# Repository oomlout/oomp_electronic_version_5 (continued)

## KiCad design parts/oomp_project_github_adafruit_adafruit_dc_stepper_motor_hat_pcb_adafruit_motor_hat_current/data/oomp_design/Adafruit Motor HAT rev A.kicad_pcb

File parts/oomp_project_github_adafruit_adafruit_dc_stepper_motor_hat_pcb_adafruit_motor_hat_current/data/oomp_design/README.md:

# OOMP KiCad design copy

Open `Adafruit Motor HAT rev A.kicad_pro` (or the `.kicad_pcb` / `.kicad_sch`) in KiCad. Local OOMP libraries are under `libraries/`. Original inputs are preserved in [../original/](../original/).

Only verified unchanged installed KiCad defaults were renamed. Modified, custom, unmatched and unavailable items remain unchanged. Soldering variants are never swapped during conversion. Existing pad coordinates, nets and UUIDs are preserved.

See [conversion_report.yaml](conversion_report.yaml) for every conversion and skip. Copy this directory before editing; regeneration refuses to overwrite edited design files.

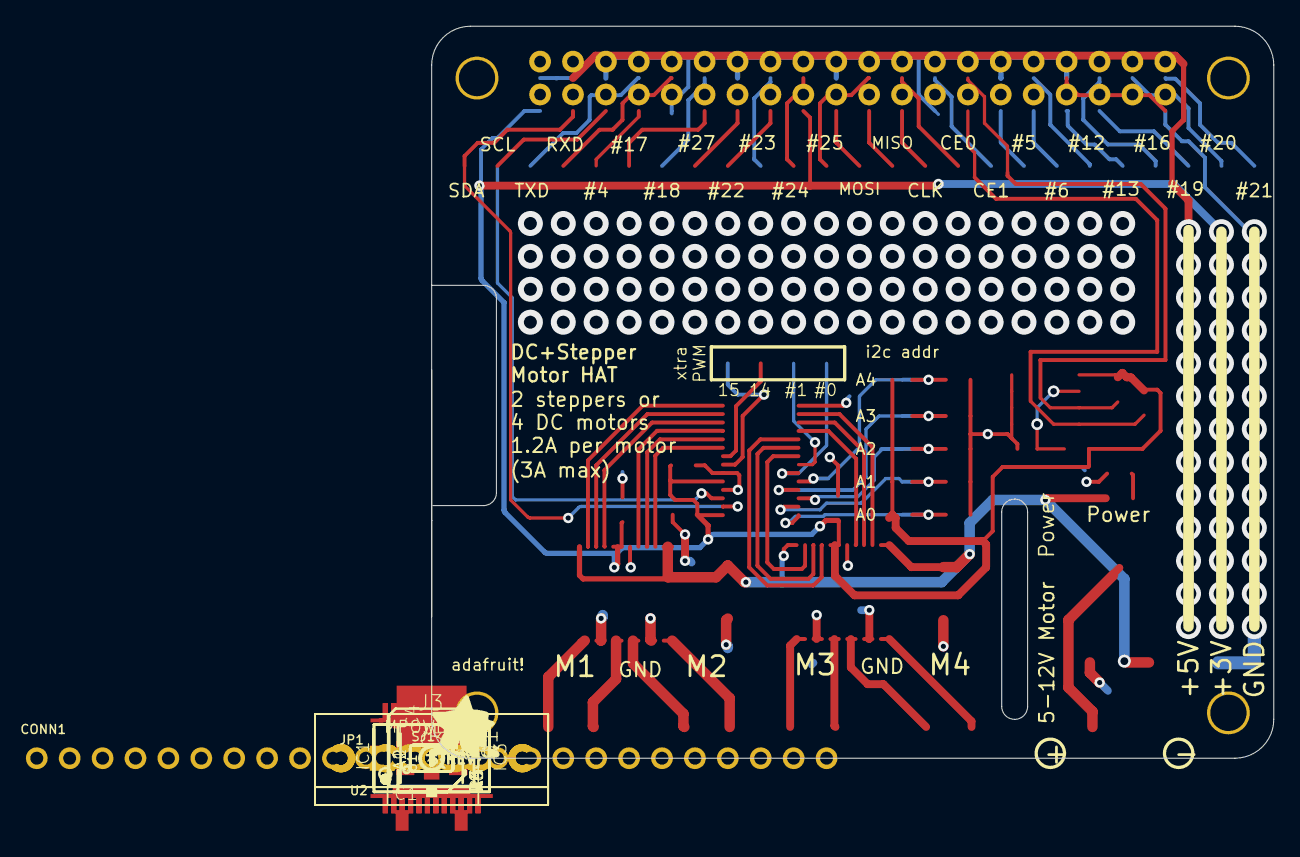
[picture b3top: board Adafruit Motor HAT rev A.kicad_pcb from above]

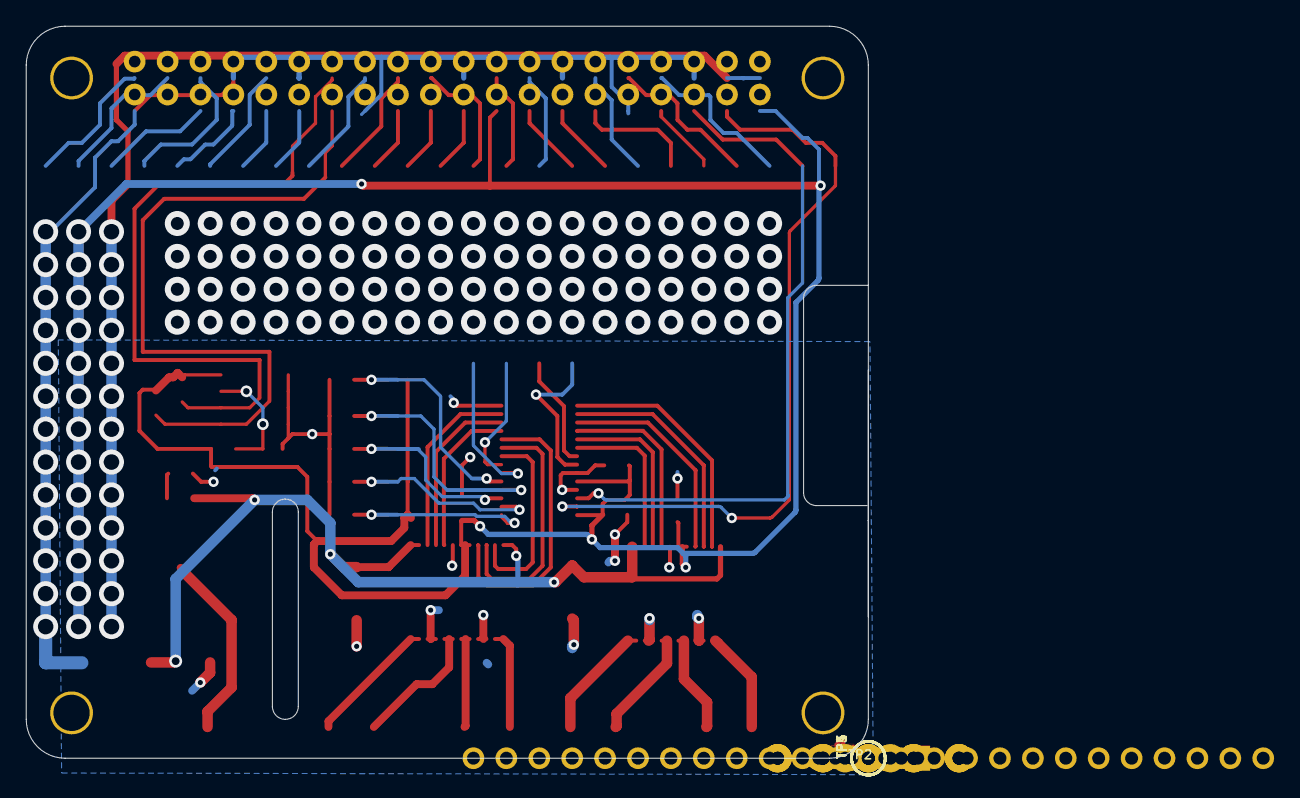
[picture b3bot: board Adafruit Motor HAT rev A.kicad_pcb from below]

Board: 2 copper layers, 65.0 x 56.5 mm, 44 parts (5 on the bottom side), 63 nets.

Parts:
A0, A1, A2, A3, A4: SOLDERJUMPER_REFLOW_NOPASTE
C1, C3: 0.1uF; 0805-NO
C4: 47uF/16v; PANASONIC_C
C5: 47uF+/16v; PANASONIC_C
C6, C10: 10uF; 0805-NO
CONN1: HEADER-1X25; 1X25_ROUND_70MIL
FID1, FID2, FID3: FIDUCIAL""; FIDUCIAL_1MM
IC1, IC3: TB6612FNG; SSOP24
J1, J3: 1X5; 1X05-3.5MM
JP1: 1X04_ROUND_76
LED1: Green; CHIPLED_0805_NOOUTLINE
MPOWER0: 1X2-3.5MM
Q1: AOD417; D-PAK_TO252AA
R1, R2, R3: 3.9K; 0805-NO
R4, R5, R6, R8, R9: 10k; 0805-NO
R7: 1K; 0805-NO
RPI1: RASPBERRYPI_BPLUS_HATSLOTS; PI_HAT_SLOTS
SJ1: WP; SOLDERJUMPER_CLOSEDWIRE
TP1, TP2, TP3, TP4, TP5: TESTPOINT_ROUND_2MM
U1: CAT24C32; SOIC8_150MIL
U2: PCA9685; TSSOP28
U$5: PIHATLOGO
U$6: PCBFEAT-REV-040
U$51: ADAFRUIT_5MM

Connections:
3.3V: A0.1, A1.1, A2.1, A3.2, A4.2, C1.1, C3.1, C6.1, C10.1, IC1.19, IC1.20, IC3.19, IC3.20, R1.2, R2.2, R3.2, RPI1.1, RPI1.17, U1.8, U2.24, U2.28
5.0V: RPI1.2, RPI1.4
+12V: C4.+, C5.+, IC1.13, IC1.14, IC1.24, IC3.13, IC3.14, IC3.24, LED1.A, Q1.3
A0: A0.2, R4.2, TP5.P$1, U2.1
A1: A1.2, R5.2, TP4.P$1, U2.2
A2: A2.2, R6.2, TP3.P$1, U2.3
A3: A3.1, R8.2, TP2.P$1, U2.4
A4: A4.1, R9.2, TP1.P$1, U2.5
EECLK: R2.1, RPI1.28, U1.6
EEDATA: R1.1, RPI1.27, U1.5
GND: C1.2, C3.2, C4.-, C5.-, C6.2, C10.2, IC1.3, IC1.4, IC1.9, IC1.10, IC1.18, IC3.3, IC3.4, IC3.9, IC3.10, IC3.18, J1.3, J3.3, MPOWER0.1, Q1.1, R4.1, R5.1, R6.1, R7.1, R8.1, R9.1, RPI1.6, RPI1.9, RPI1.14, RPI1.20, RPI1.25, RPI1.30, RPI1.34, RPI1.39, SJ1.1, U1.1, U1.2, U1.3, U1.4, U2.14, U2.23, U2.25
GPIO4: CONN1.5, RPI1.7
GPIO5: CONN1.18, RPI1.29
GPIO6: CONN1.19, RPI1.31
GPIO12: CONN1.20, RPI1.32
GPIO13: CONN1.21, RPI1.33
GPIO16: CONN1.22, RPI1.36
GPIO17: CONN1.6, RPI1.11
GPIO18: CONN1.7, RPI1.12
GPIO19: CONN1.23, RPI1.35
GPIO20: CONN1.24, RPI1.38
GPIO21: CONN1.25, RPI1.40
GPIO22: CONN1.9, RPI1.15
GPIO23: CONN1.10, RPI1.16
GPIO24: CONN1.11, RPI1.18
GPIO25: CONN1.12, RPI1.22
GPIO27: CONN1.8, RPI1.13
unnamed: MPOWER0.2, Q1.4
unnamed: IC1.1, IC1.2, J1.5
unnamed: IC1.5, IC1.6, J1.4
unnamed: IC1.7, IC1.8, J1.2
unnamed: IC1.11, IC1.12, J1.1
unnamed: IC3.1, IC3.2, J3.5
unnamed: IC3.5, IC3.6, J3.4
unnamed: IC3.7, IC3.8, J3.2
unnamed: R3.1, SJ1.2, U1.7
unnamed: IC3.11, IC3.12, J3.1
unnamed: LED1.C, R7.2
PWM0: JP1.1, U2.6
PWM1: JP1.2, U2.7
PWM2: IC3.23, U2.8
PWM3: IC3.22, U2.9
PWM4: IC3.21, U2.10
PWM5: IC3.17, U2.11
PWM6: IC3.16, U2.12
PWM7: IC3.15, U2.13
PWM8: IC1.23, U2.15
PWM9: IC1.22, U2.16
PWM10: IC1.21, U2.17
PWM11: IC1.17, U2.18
PWM12: IC1.16, U2.19
PWM13: IC1.15, U2.20
PWM14: JP1.3, U2.21
PWM15: JP1.4, U2.22
RXD: CONN1.4, RPI1.10
SCL: CONN1.2, RPI1.5, U2.26
SDA: CONN1.1, RPI1.3, U2.27
SPI_CE0: CONN1.16, RPI1.24
SPI_CE1: CONN1.17, RPI1.26
SPI_MISO: CONN1.14, RPI1.21
SPI_MOSI: CONN1.13, RPI1.19
SPI_SCLK: CONN1.15, RPI1.23
TXD: CONN1.3, RPI1.8

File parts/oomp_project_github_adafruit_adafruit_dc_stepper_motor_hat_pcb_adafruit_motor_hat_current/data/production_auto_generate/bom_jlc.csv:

Comment,Designator,Footprint,LCSC Part #
,JP1,Adafruit Motor HAT rev A-import-fps:1X04_ROUND_76,C42431795
,U$51,Adafruit Motor HAT rev A-import-fps:ADAFRUIT_5MM,
,U$6,Adafruit Motor HAT rev A-import-fps:PCBFEAT-REV-040,
,U$5,Adafruit Motor HAT rev A-import-fps:PIHATLOGO,
,"A0,A1,A2,A3,A4",Adafruit Motor HAT rev A-import-fps:SOLDERJUMPER_REFLOW_NOPASTE,
,"TP1,TP2,TP3,TP4,TP5",Adafruit Motor HAT rev A-import-fps:TESTPOINT_ROUND_2MM,
0.1uF,"C1,C3",Adafruit Motor HAT rev A-import-fps:0805-NO,
10k,"R4,R5,R6,R8,R9",Adafruit Motor HAT rev A-import-fps:0805-NO,C17414
10uF,"C6,C10",Adafruit Motor HAT rev A-import-fps:0805-NO,
1K,R7,Adafruit Motor HAT rev A-import-fps:0805-NO,C17513
1X2-3.5MM,MPOWER0,Adafruit Motor HAT rev A-import-fps:1X2-3.5MM,C492401
1X5,"J1,J3",Adafruit Motor HAT rev A-import-fps:1X05-3.5MM,C42431835
3.9K,"R1,R2,R3",Adafruit Motor HAT rev A-import-fps:0805-NO,C2907252
47uF+/16v,C5,Adafruit Motor HAT rev A-import-fps:PANASONIC_C,
47uF/16v,C4,Adafruit Motor HAT rev A-import-fps:PANASONIC_C,
AOD417,Q1,Adafruit Motor HAT rev A-import-fps:D-PAK_TO252AA,
CAT24C32,U1,Adafruit Motor HAT rev A-import-fps:SOIC8_150MIL,
Green,LED1,Adafruit Motor HAT rev A-import-fps:CHIPLED_0805_NOOUTLINE,
HEADER-1X25,CONN1,Adafruit Motor HAT rev A-import-fps:1X25_ROUND_70MIL,C2883713
PCA9685,U2,Adafruit Motor HAT rev A-import-fps:TSSOP28,
RASPBERRYPI_BPLUS_HATSLOTS,RPI1,Adafruit Motor HAT rev A-import-fps:PI_HAT_SLOTS,
TB6612FNG,"IC1,IC3",Adafruit Motor HAT rev A-import-fps:SSOP24,

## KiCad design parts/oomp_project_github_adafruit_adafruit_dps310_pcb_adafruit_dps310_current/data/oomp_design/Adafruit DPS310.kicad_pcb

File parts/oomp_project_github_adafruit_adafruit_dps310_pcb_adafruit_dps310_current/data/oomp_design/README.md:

# OOMP KiCad design copy

Open `Adafruit DPS310.kicad_pro` (or the `.kicad_pcb` / `.kicad_sch`) in KiCad. Local OOMP libraries are under `libraries/`. Original inputs are preserved in [../original/](../original/).

Only verified unchanged installed KiCad defaults were renamed. Modified, custom, unmatched and unavailable items remain unchanged. Soldering variants are never swapped during conversion. Existing pad coordinates, nets and UUIDs are preserved.

See [conversion_report.yaml](conversion_report.yaml) for every conversion and skip. Copy this directory before editing; regeneration refuses to overwrite edited design files.

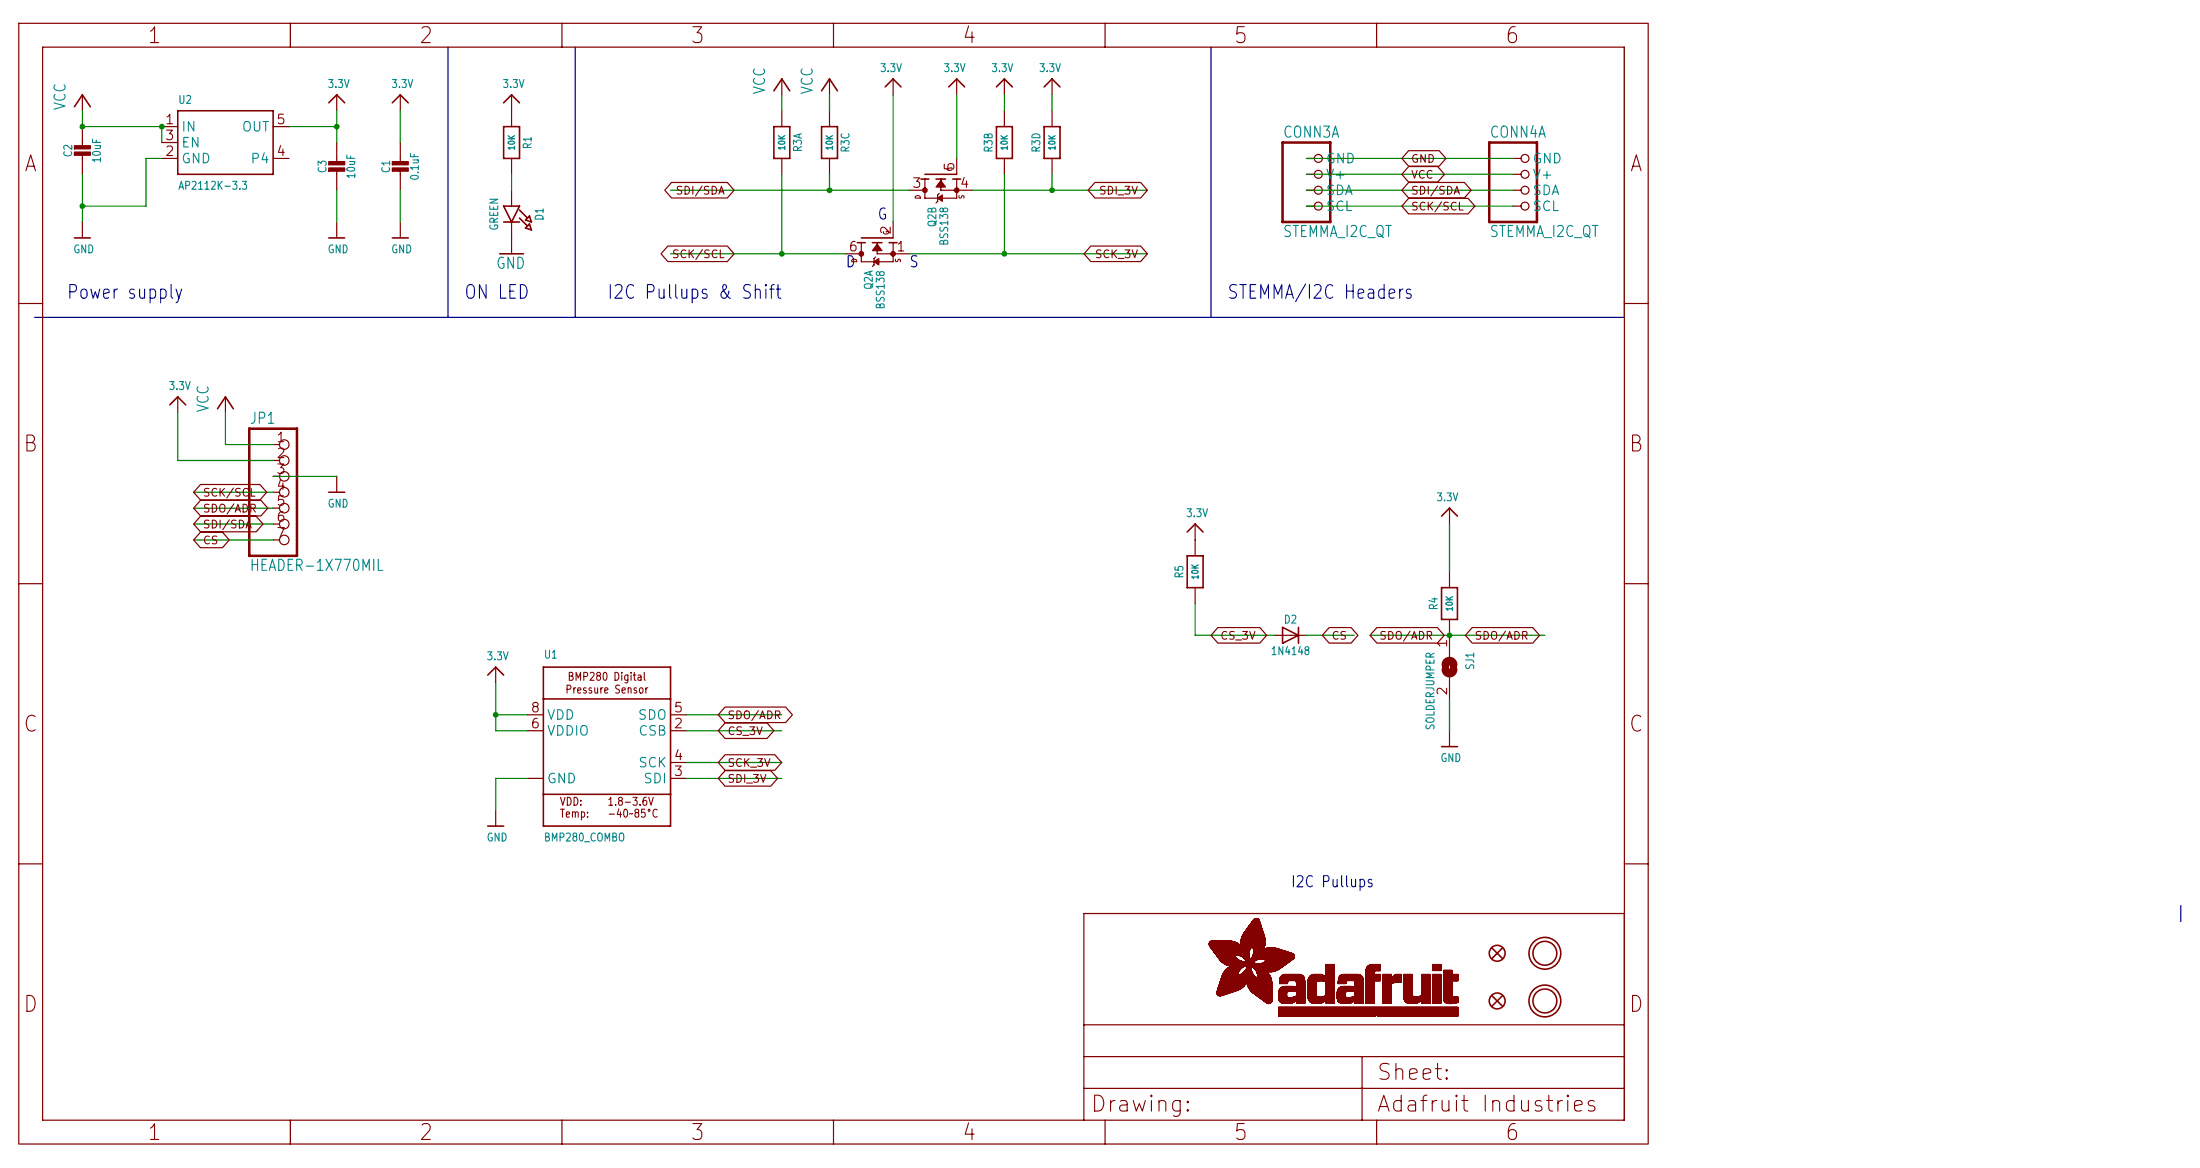
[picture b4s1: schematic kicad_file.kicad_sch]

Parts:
C1: 0.1uF; 0603-NO
C2, C3: 10uF; 0805-NO
CONN3, CONN4: STEMMA_I2C_QT; JST_SH4
D1: GREEN; CHIPLED_0603_NOOUTLINE
D2: 1N4148; SOD-323
FID3, FID4: FIDUCIAL_1MM
JP1: HEADER-1X770MIL; 1X07_ROUND_70
Q2: BSS138; SOT363
R1, R4, R5: 10K; 0603-NO
R3: 10K; RESPACK_4X0603
SJ1: SOLDERJUMPER; SOLDERJUMPER_ARROW_NOPASTE
U1: BMP280_COMBO; BMX280_COMBO
U2: AP2112K-3.3; SOT23-5
U$1, U$17: MOUNTINGHOLE2.5; MOUNTINGHOLE_2.5_PLATED

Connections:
3.3V: C1.1, C3.1, JP1.2, Q2.2 (G), Q2.5 (G), R1.1, R3.2 (1), R3.4 (1), R4.2, R5.2, U1.6 (VDDIO), U1.8 (VDD), U2.5 (OUT)
CS: D2.C, JP1.7
CS_3V: D2.A, R5.1, U1.2 (CSB)
GND: C1.2, C2.2, C3.2, CONN3.1 (GND), CONN4.1 (GND), D1.C, JP1.3, SJ1.2, U1.1 (GND), U1.7 (GND), U2.2 (GND)
unnamed: D1.A, R1.2
SCK/SCL: CONN3.4 (SCL), CONN4.4 (SCL), JP1.4, Q2.6 (D), R3.8 (2)
SCK_3V: Q2.1 (S), R3.7 (2), U1.4 (SCK)
SDI/SDA: CONN3.3 (SDA), CONN4.3 (SDA), JP1.6, Q2.3 (D), R3.6 (2)
SDI_3V: Q2.4 (S), R3.5 (2), U1.3 (SDI)
SDO/ADR: JP1.5, R4.1, SJ1.1, U1.5 (SDO)
VCC: C2.1, CONN3.2 (V+), CONN4.2 (V+), JP1.1, R3.1, R3.3 (1), U2.1 (IN), U2.3 (EN)

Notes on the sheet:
STEMMA/I2C Headers
ON LED
I2C Pullups & Shift
I2C Pullups
Power supply

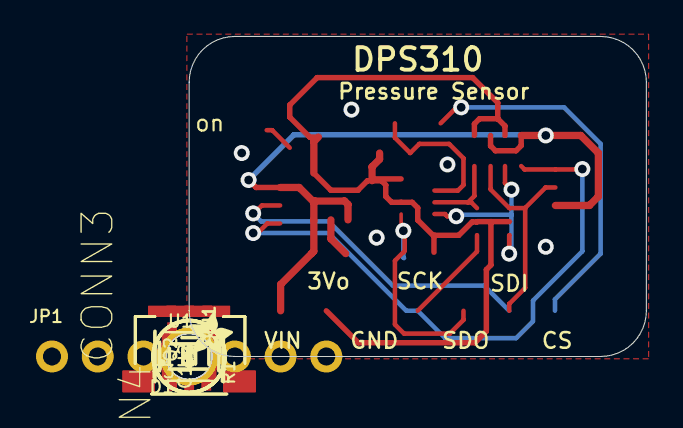
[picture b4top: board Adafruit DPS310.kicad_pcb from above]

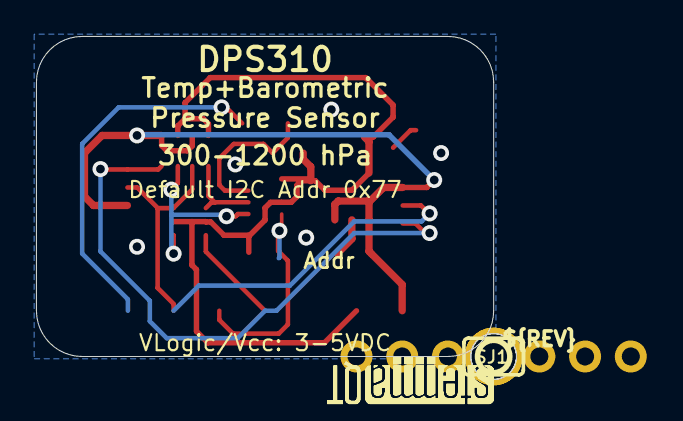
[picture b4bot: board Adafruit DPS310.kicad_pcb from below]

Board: 2 copper layers, 25.4 x 17.8 mm, 26 parts (4 on the bottom side), 11 nets.

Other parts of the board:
U$4: ADAFRUIT_2.5MM
U$25: PCBFEAT-REV-040
U$30, U$31: STEMMAQT
UNK_HOLE_0: dummyfp0
UNK_HOLE_1: dummyfp1

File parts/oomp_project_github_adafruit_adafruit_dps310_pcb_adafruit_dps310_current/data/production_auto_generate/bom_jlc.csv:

Comment,Designator,Footprint,LCSC Part #
,JP1,Adafruit DPS310-import-fps:1X07_ROUND_70,C7501585
,U$4,Adafruit DPS310-import-fps:ADAFRUIT_2.5MM,
,U1,Adafruit DPS310-import-fps:BMX280_COMBO,
,U$25,Adafruit DPS310-import-fps:PCBFEAT-REV-040,
,"U$30,U$31",Adafruit DPS310-import-fps:STEMMAQT,
0.1uF,C1,Adafruit DPS310-import-fps:0603-NO,C14663
10K,"R1,R4,R5",Adafruit DPS310-import-fps:0603-NO,C98220
10K,R3,Adafruit DPS310-import-fps:RESPACK_4X0603,C98220
10uF,"C2,C3",Adafruit DPS310-import-fps:0805-NO,
1N4148,D2,Adafruit DPS310-import-fps:SOD-323,
AP2112K-3.3,U2,Adafruit DPS310-import-fps:SOT23-5,
BSS138,Q2,Adafruit DPS310-import-fps:SOT363,
GREEN,D1,Adafruit DPS310-import-fps:CHIPLED_0603_NOOUTLINE,
STEMMA_I2C_QT,"CONN3,CONN4",Adafruit DPS310-import-fps:JST_SH4,C160404

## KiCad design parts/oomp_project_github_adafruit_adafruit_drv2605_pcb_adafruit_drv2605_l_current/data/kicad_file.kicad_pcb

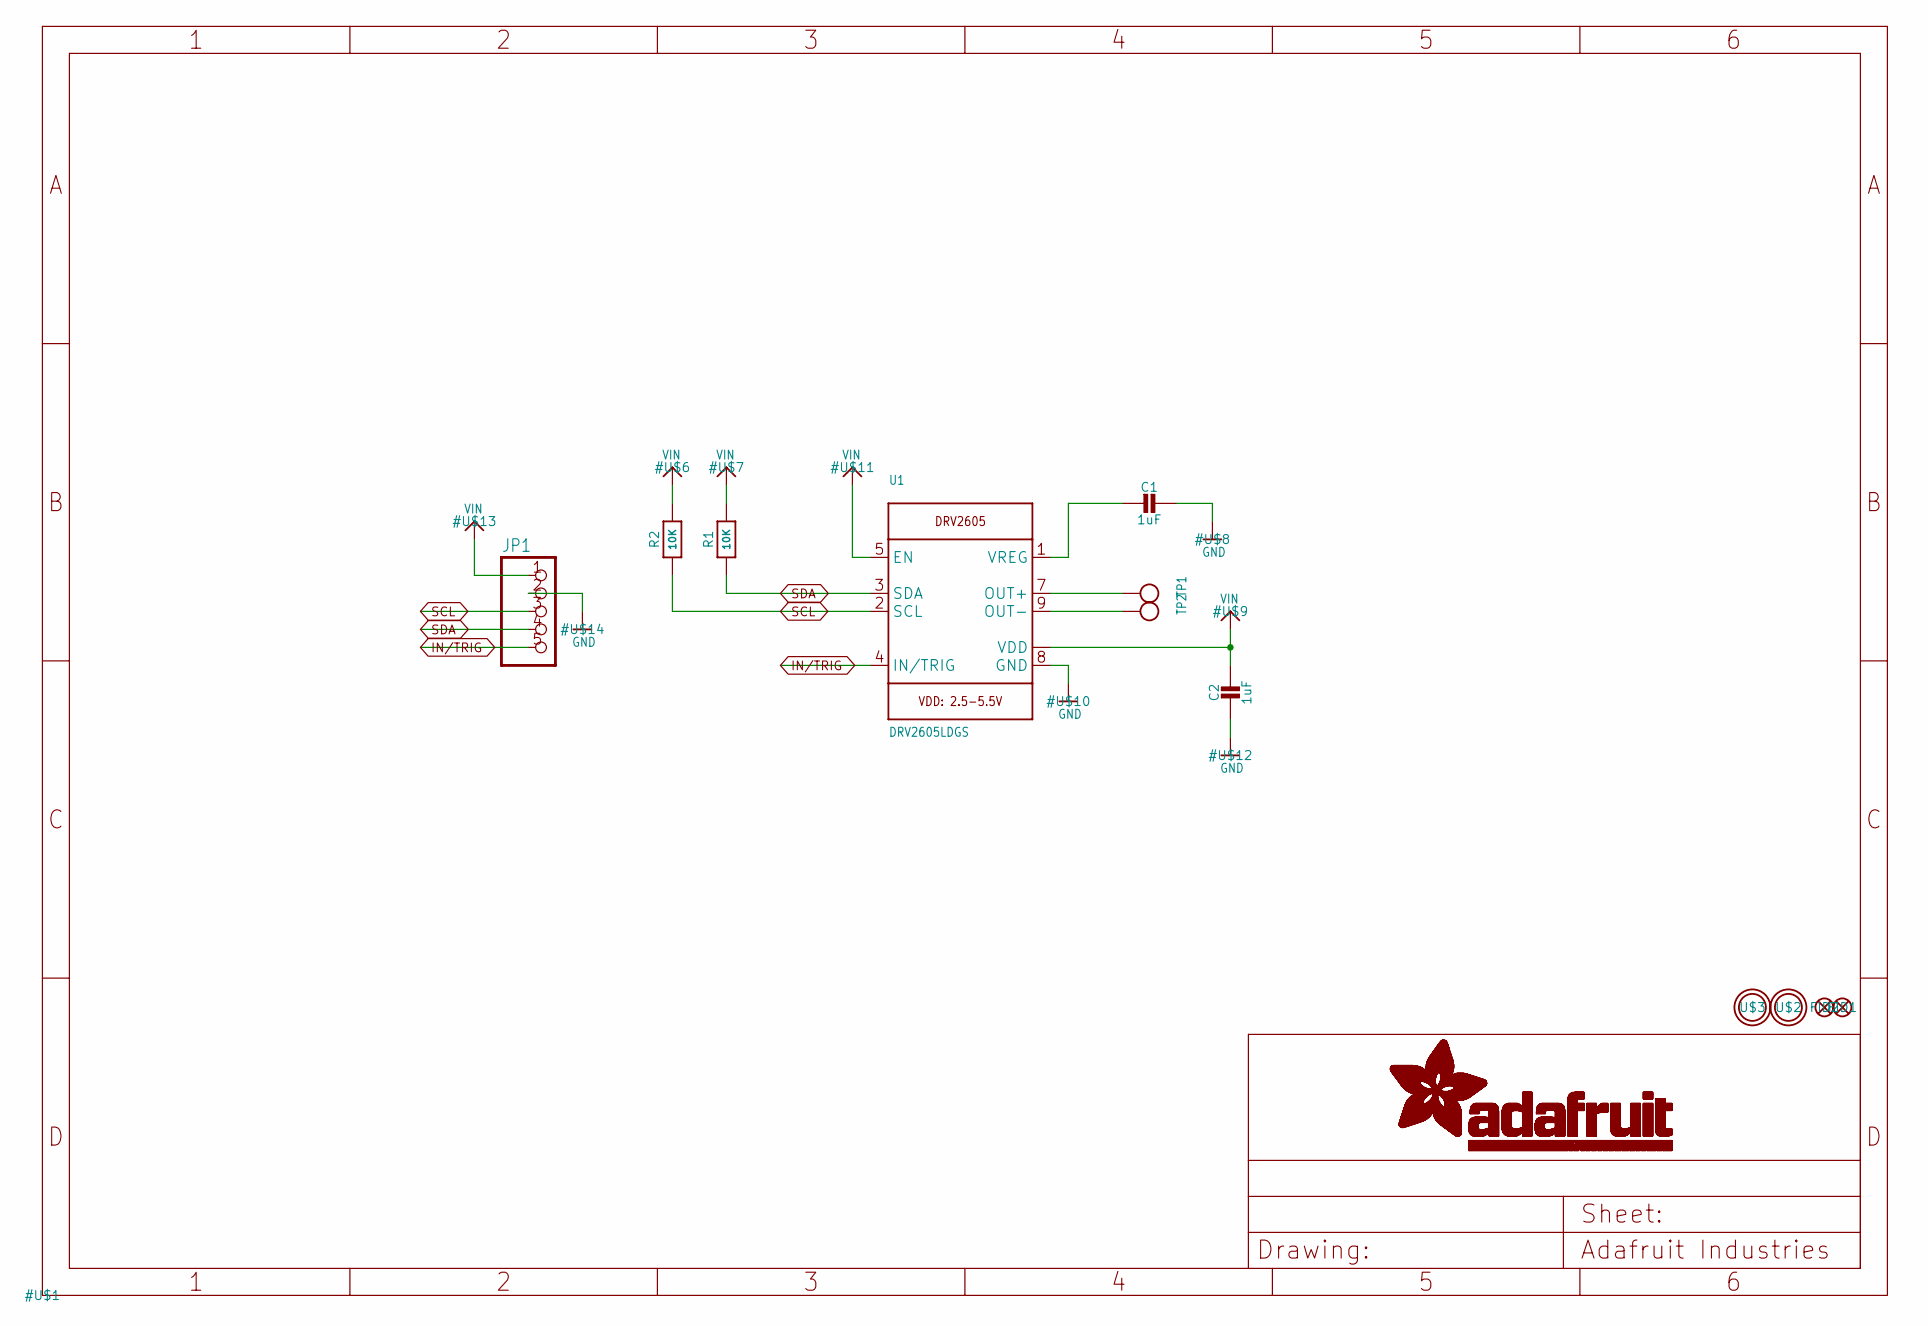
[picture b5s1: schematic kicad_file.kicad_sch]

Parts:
C1, C2: 1uF; 0805-NO
FID1, FID2: FIDUCIAL""; FIDUCIAL_1MM
JP1: HEADER-1X576MIL_FULL; 1X05_ROUND_FULL_76
R1, R2: 10K; 0805-NO
TP1, TP2: TESTPOINTPAD2MM; TESTPOINT_PAD_2MM
U1: DRV2605LDGS; PSOP10
U$2, U$3: MOUNTINGHOLE2.5; MOUNTINGHOLE_2.5_PLATED

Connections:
GND: C1.1, C2.2, JP1.2, U1.8 (GND)
IN/TRIG: JP1.5, U1.4 (IN/TRIG)
unnamed: C1.2, U1.1 (VREG)
OUT+: TP1.P$1, U1.7 (OUT+)
OUT-: TP2.P$1, U1.9 (OUT-)
SCL: JP1.3, R2.1, U1.2 (SCL)
SDA: JP1.4, R1.1, U1.3 (SDA)
VIN: C2.1, JP1.1, R1.2, R2.2, U1.5 (EN), U1.6 (VDD), U1.10 (VDD)

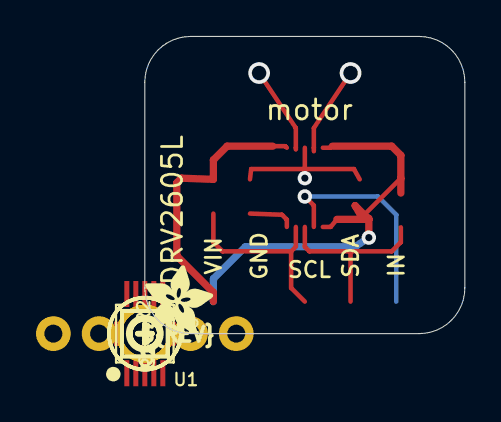
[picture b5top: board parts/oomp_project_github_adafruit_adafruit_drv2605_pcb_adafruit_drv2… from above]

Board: 2 copper layers, 17.8 x 16.5 mm, 16 parts (0 on the bottom side), 8 nets.

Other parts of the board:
U$4: SYMBOL_PLUS
U$5: SYMBOL_MINUS
U$15: PCBFEAT-REV-040
U$18: ADAFRUIT_3.5MM

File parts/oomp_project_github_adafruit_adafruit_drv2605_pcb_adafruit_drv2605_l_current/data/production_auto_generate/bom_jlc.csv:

Comment,Designator,Footprint,LCSC Part #
,JP1,Adafruit DRV2605L-import-fps:1X05_ROUND_FULL_76,C42431835
,U$18,Adafruit DRV2605L-import-fps:ADAFRUIT_3.5MM,
,U$15,Adafruit DRV2605L-import-fps:PCBFEAT-REV-040,
,U$5,Adafruit DRV2605L-import-fps:SYMBOL_MINUS,
,U$4,Adafruit DRV2605L-import-fps:SYMBOL_PLUS,
,"TP1,TP2",Adafruit DRV2605L-import-fps:TESTPOINT_PAD_2MM,
10K,"R1,R2",Adafruit DRV2605L-import-fps:0805-NO,C17414
1uF,"C1,C2",Adafruit DRV2605L-import-fps:0805-NO,
DRV2605LDGS,U1,Adafruit DRV2605L-import-fps:PSOP10,

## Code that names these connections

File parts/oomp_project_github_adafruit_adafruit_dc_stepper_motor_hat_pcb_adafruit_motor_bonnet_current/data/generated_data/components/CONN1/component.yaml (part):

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      position:
        x: 314.96
        y: 78.74
      net: GPIO4
      net_aliases:
      - GPIO4
      net_scope: global
      no_connect: false
      connected_to:
      - reference: RPI1
        pin_number: '7'
        pin_name: GPIO4
      - reference: RPI1
        pin_number: S7
        pin_name: GPIO4
    - number: '6'
      name: '6'
      electrical_type: passive
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      position:
        x: 314.96
        y: 81.28
      net: GPIO17
      net_aliases:
      - GPIO17
      net_scope: global
      no_connect: false
      connected_to:
      - reference: RPI1
        pin_number: '11'
        pin_name: GPIO17
      - reference: RPI1
        pin_number: S11
        pin_name: GPIO17
    - number: '7'
      name: '7'
      electrical_type: passive
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      position:
        x: 314.96
        y: 83.82
      net: GPIO18
      net_aliases:
      - GPIO18
      net_scope: global
      no_connect: false
      connected_to:
      - reference: RPI1
        pin_number: '12'
        pin_name: GPIO18
      - reference: RPI1
        pin_number: S12
        pin_name: GPIO18
    - number: '8'
      name: '8'
      electrical_type: passive
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      position:
        x: 314.96
        y: 86.36
      net: GPIO27
      net_aliases:
      - GPIO27
      net_scope: global
      no_connect: false
      connected_to:
      - reference: RPI1
        pin_number: '13'
        pin_name: GPIO27
      - reference: RPI1
        pin_number: S13
        pin_name: GPIO27
    - number: '9'
      name: '9'
      electrical_type: passive
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      position:
        x: 314.96
        y: 88.9
      net: GPIO22
      net_aliases:
      - GPIO22
      net_scope: global
      no_connect: false
      connected_to:
      - reference: RPI1
        pin_number: '15'
        pin_name: GPIO22
      - reference: RPI1
        pin_number: S15
        pin_name: GPIO22
    - number: '10'
      name: '10'
      electrical_type: passive
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      position:
        x: 314.96
        y: 91.44
      net: GPIO23
      net_aliases:
      - GPIO23
      net_scope: global
      no_connect: false
      connected_to:
      - reference: RPI1
        pin_number: '16'
        pin_name: GPIO23
      - reference: RPI1
        pin_number: S16
        pin_name: GPIO23
    - number: '11'
      name: '11'
      electrical_type: passive
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      position:
        x: 314.96
        y: 93.98
      net: GPIO24
      net_aliases:
      - GPIO24
      net_scope: global
      no_connect: false
      connected_to:
      - reference: RPI1
        pin_number: '18'
        pin_name: GPIO24
      - reference: RPI1
        pin_number: S18
        pin_name: GPIO24
    - number: '12'
      name: '12'
      electrical_type: passive
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      position:
        x: 314.96
        y: 96.52
      net: GPIO25
      net_aliases:
      - GPIO25
      net_scope: global
      no_connect: false
      connected_to:
      - reference: RPI1
        pin_number: '22'
        pin_name: GPIO25
      - reference: RPI1
        pin_number: S22
        pin_name: GPIO25
    - number: '13'
      name: '13'
      electrical_type: passive
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      connected_to:
      - reference: RPI1
        pin_number: '19'
        pin_name: SPI_MOSI
      - reference: RPI1
        pin_number: S19
        pin_name: SPI_MOSI
    - number: '14'
      name: '14'
      electrical_type: passive
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      connected_to:
      - reference: RPI1
        pin_number: '21'
        pin_name: SPI_MISO
      - reference: RPI1
        pin_number: S21
        pin_name: SPI_MISO
    - number: '15'
      name: '15'
      electrical_type: passive
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      connected_to:
      - reference: RPI1
        pin_number: '23'
        pin_name: SPI_SCLK
      - reference: RPI1
        pin_number: S23
        pin_name: SPI_SCLK
    - number: '16'
      name: '16'
      electrical_type: passive
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      connected_to:
      - reference: RPI1
        pin_number: '24'
        pin_name: '#SPI_CE0'
      - reference: RPI1
        pin_number: S24
        pin_name: '#SPI_CE0'
    - number: '17'
      name: '17'
      electrical_type: passive
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      connected_to:
      - reference: RPI1
        pin_number: '26'
        pin_name: '#SPI_CE1'
      - reference: RPI1
        pin_number: S26
        pin_name: '#SPI_CE1'
    - number: '18'
      name: '18'
      electrical_type: passive
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      position:
        x: 314.96
        y: 111.76
      net: GPIO5
      net_aliases:
      - GPIO5
      net_scope: global
      no_connect: false
      connected_to:
      - reference: RPI1
        pin_number: '29'
        pin_name: GPIO5
      - reference: RPI1
        pin_number: S29
        pin_name: GPIO5
    - number: '19'
      name: '19'
      electrical_type: passive
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      position:
        x: 314.96
        y: 114.3
      net: GPIO6
      net_aliases:
      - GPIO6
      net_scope: global
      no_connect: false
      connected_to:
      - reference: RPI1
        pin_number: '31'
        pin_name: GPIO6
      - reference: RPI1
        pin_number: S31
        pin_name: GPIO6
    - number: '20'
      name: '20'
      electrical_type: passive
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      position:
        x: 314.96
        y: 116.84
      net: GPIO12
      net_aliases:
      - GPIO12
      net_scope: global
      no_connect: false
      connected_to:
      - reference: RPI1
        pin_number: '32'
        pin_name: GPIO12
      - reference: RPI1
        pin_number: S32
        pin_name: GPIO12
    - number: '21'
      name: '21'
      electrical_type: passive
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      position:
        x: 314.96
        y: 119.38
      net: GPIO13
      net_aliases:
      - GPIO13
      net_scope: global
      no_connect: false
      connected_to:
      - reference: RPI1
        pin_number: '33'
        pin_name: GPIO13
      - reference: RPI1
        pin_number: S33
        pin_name: GPIO13
    - number: '22'
      name: '22'
      electrical_type: passive
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      position:
        x: 314.96
        y: 121.92
      net: GPIO16
      net_aliases:
      - GPIO16
      net_scope: global
      no_connect: false
      connected_to:
      - reference: RPI1
        pin_number: '36'
        pin_name: GPIO16
      - reference: RPI1
        pin_number: S36
        pin_name: GPIO16
    - number: '23'
      name: '23'
      electrical_type: passive
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      position:
        x: 314.96
        y: 124.46
      net: GPIO19
      net_aliases:
      - GPIO19
      net_scope: global
      no_connect: false
      connected_to:
      - reference: RPI1
        pin_number: '35'
        pin_name: GPIO19
      - reference: RPI1
        pin_number: S35
        pin_name: GPIO19
    - number: '24'
      name: '24'
      electrical_type: passive
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      position:
        x: 314.96
        y: 127.0
      net: GPIO20
      net_aliases:
      - GPIO20
      net_scope: global
      no_connect: false
      connected_to:
      - reference: RPI1
        pin_number: '38'
        pin_name: GPIO20
      - reference: RPI1
        pin_number: S38
        pin_name: GPIO20
    - number: '25'
      name: '25'
      electrical_type: passive
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      position:
        x: 314.96
        y: 129.54
      net: GPIO21
      net_aliases:
      - GPIO21
      net_scope: global
      no_connect: false
      connected_to:
      - reference: RPI1
        pin_number: '40'
        pin_name: GPIO21
      - reference: RPI1
        pin_number: S40
        pin_name: GPIO21
    size:
      local_graphics:
        measurement: symbol graphics only; excludes pins, properties, and text
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    pin_name: RXD
  - reference: RPI1
    pin_number: '11'
    pin_name: GPIO17
  - reference: RPI1
    pin_number: '12'
    pin_name: GPIO18
  - reference: RPI1
    pin_number: '13'
    pin_name: GPIO27
  - reference: RPI1
    pin_number: '15'
    pin_name: GPIO22
  - reference: RPI1
    pin_number: '16'
    pin_name: GPIO23
  - reference: RPI1
    pin_number: '18'
    pin_name: GPIO24
  - reference: RPI1
    pin_number: '19'
    pin_name: SPI_MOSI
  - reference: RPI1
    pin_number: '21'
    pin_name: SPI_MISO
  - reference: RPI1
    pin_number: '22'
    pin_name: GPIO25
  - reference: RPI1
    pin_number: '23'
    pin_name: SPI_SCLK
  - reference: RPI1
    pin_number: '24'
    pin_name: '#SPI_CE0'
  - reference: RPI1
    pin_number: '26'
    pin_name: '#SPI_CE1'
  - reference: RPI1
    pin_number: '29'
    pin_name: GPIO5
  - reference: RPI1
    pin_number: '3'
    pin_name: SDA
  - reference: RPI1
    pin_number: '31'
    pin_name: GPIO6
  - reference: RPI1
    pin_number: '32'
    pin_name: GPIO12
  - reference: RPI1
    pin_number: '33'
    pin_name: GPIO13
  - reference: RPI1
    pin_number: '35'
    pin_name: GPIO19
  - reference: RPI1
    pin_number: '36'
    pin_name: GPIO16
  - reference: RPI1
    pin_number: '38'
    pin_name: GPIO20
  - reference: RPI1
    pin_number: '40'
    pin_name: GPIO21
  - reference: RPI1
    pin_number: '5'
    pin_name: SCL
  - reference: RPI1
    pin_number: '7'
    pin_name: GPIO4
  - reference: RPI1
    pin_number: '8'
    pin_name: TXD
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    pin_name: RXD
  - reference: RPI1
    pin_number: S11
    pin_name: GPIO17
  - reference: RPI1
    pin_number: S12
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
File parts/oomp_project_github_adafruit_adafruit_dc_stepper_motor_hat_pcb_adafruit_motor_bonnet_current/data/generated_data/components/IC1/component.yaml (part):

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      connected_to:
      - reference: U2
        pin_number: '20'
        pin_name: PWM13
    - number: '16'
      name: BIN2
      electrical_type: input
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      connected_to:
      - reference: U2
        pin_number: '19'
        pin_name: PWM12
    - number: '17'
      name: BIN1
      electrical_type: input
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      connected_to:
      - reference: U2
        pin_number: '18'
        pin_name: PWM11
    - number: '18'
      name: GND
      electrical_type: power_in
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      connected_to:
      - reference: U2
        pin_number: '17'
        pin_name: PWM10
    - number: '22'
      name: AIN2
      electrical_type: input
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    pin_name: PWM9
  - reference: U2
    pin_number: '17'
    pin_name: PWM10
  - reference: U2
    pin_number: '18'
    pin_name: PWM11
  - reference: U2
    pin_number: '19'
    pin_name: PWM12
  - reference: U2
    pin_number: '20'
    pin_name: PWM13
  - reference: U2
    pin_number: '23'
    pin_name: '#OE'
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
